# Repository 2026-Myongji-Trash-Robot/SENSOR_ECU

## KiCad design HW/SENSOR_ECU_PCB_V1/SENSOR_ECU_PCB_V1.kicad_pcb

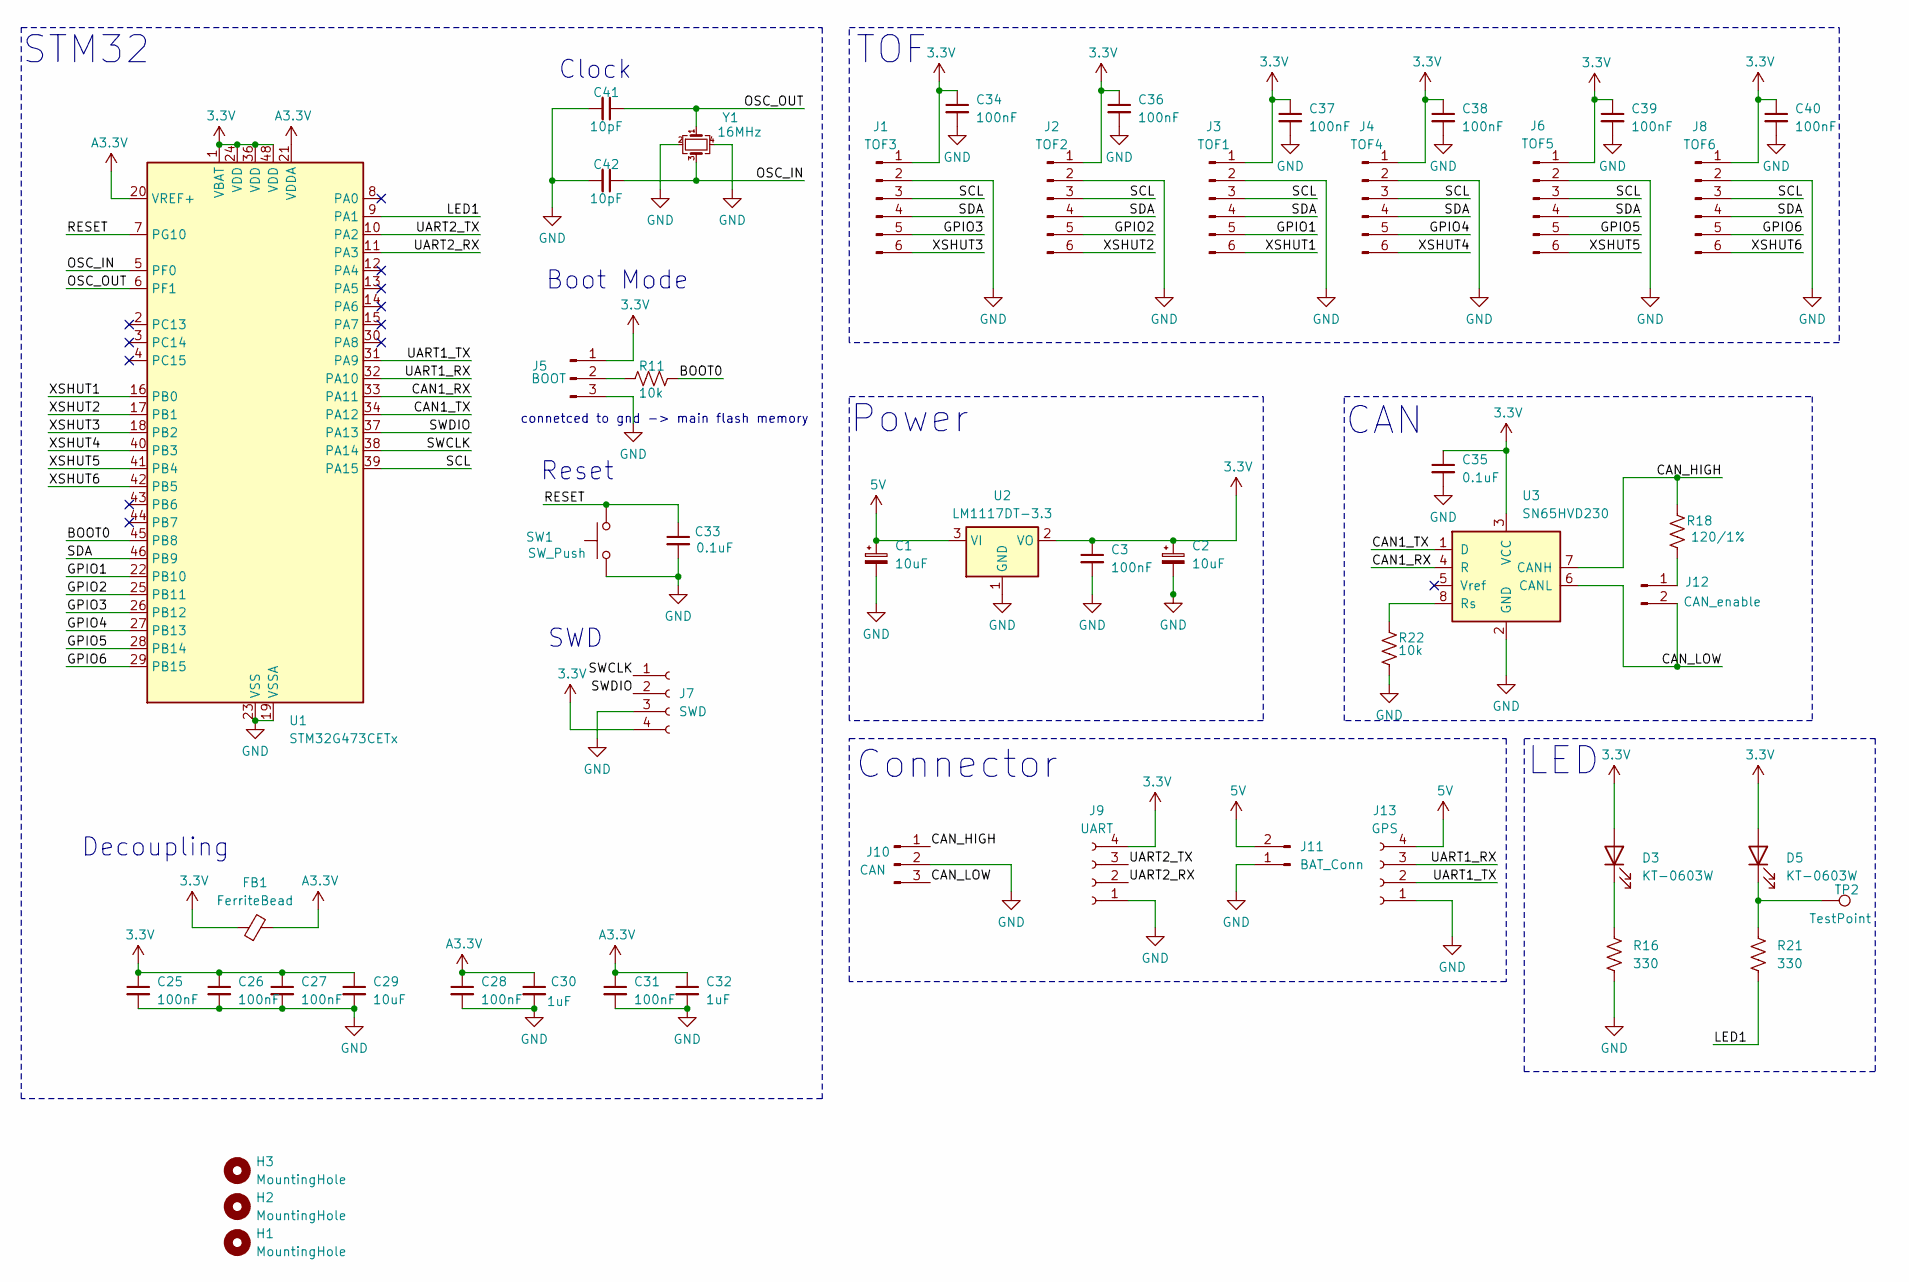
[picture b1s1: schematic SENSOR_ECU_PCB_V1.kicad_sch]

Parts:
C1, C2: 10uF; C_0603_1608Metric_Pad1.08x0.95mm_HandSolder
C3: 100nF; C_0603_1608Metric_Pad1.08x0.95mm_HandSolder
C25, C26, C27, C28, C34, C36, C37, C38: 100nF; C_0603_1608Metric; LCSC C14663
C29: 10uF; C_0603_1608Metric
C30, C32: 1uF; C_0603_1608Metric
C31, C39, C40: 100nF; C_0603_1608Metric
C33, C35: 0.1uF; C_0603_1608Metric
C41, C42: 10pF; C_0402_1005Metric_Pad0.74x0.62mm_HandSolder; LCSC C32949
D3, D5: KT-0603W; LED_0603_1608Metric; LCSC C2290
FB1: FerriteBead; L_0603_1608Metric; LCSC C1002
H1, H2, H3: MountingHole; MountingHole_3.2mm_M3
J1: TOF3; Molex_SPOX_5268-06A_1x06_P2.50mm_Horizontal
J2: TOF2; Molex_SPOX_5268-06A_1x06_P2.50mm_Horizontal
J3: TOF1; Molex_SPOX_5268-06A_1x06_P2.50mm_Horizontal
J4: TOF4; Molex_SPOX_5268-06A_1x06_P2.50mm_Horizontal
J5: BOOT; PinHeader_1x03_P2.54mm_Vertical
J6: TOF5; Molex_SPOX_5268-06A_1x06_P2.50mm_Horizontal
J7: SWD; PinHeader_1x04_P2.54mm_Horizontal
J8: TOF6; Molex_SPOX_5268-06A_1x06_P2.50mm_Horizontal
J9: UART; PinHeader_1x04_P2.54mm_Horizontal
J10: CAN; Wago_734-163_1x03_P3.50mm_Horizontal
J11: BAT_Conn; Wago_734-162_1x02_P3.50mm_Horizontal
J12: CAN_enable; PinHeader_1x02_P2.54mm_Vertical
J13: GPS; PinHeader_1x04_P2.54mm_Horizontal
R11, R22: 10k; R_0603_1608Metric; LCSC C15401
R16, R21: 330; R_0603_1608Metric; LCSC C23138
R18: 120/1%; R_0603_1608Metric; LCSC C22787
SW1: SW_Push; SW_PUSH_6mm_H7.3mm; LCSC C255812
TP2: TestPoint; TestPoint_Pad_D1.0mm
U1: STM32G473CETx; LQFP-48_7x7mm_P0.5mm; LCSC C730113
U2: LM1117DT-3.3; TO-252-2; LCSC C969102
U3: SN65HVD230; SOIC-8_3.9x4.9mm_P1.27mm; LCSC C12084
Y1: 16MHz; Crystal_SMD_3225-4Pin_3.2x2.5mm; LCSC C13738

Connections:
3.3V: C2.1, C3.1, C25.1, C26.1, C27.1, C29.1, C34.1, C35.1, C36.1, C37.1, C38.1, C39.1, C40.1, D3.2 (A), D5.2 (A), FB1.1, J1.1, J2.1, J3.1, J4.1, J5.1, J6.1, J7.4, J8.1, J9.4, U1.1 (VBAT), U1.24 (VDD), U1.36 (VDD), U1.48 (VDD), U2.2 (VO), U3.3 (VCC)
5V: C1.1, J11.2, J13.4, U2.3 (VI)
/BOOT0: R11.2, U1.45 (PB8)
/CAN1_RX: U1.33 (PA11), U3.4 (R)
/CAN1_TX: U1.34 (PA12), U3.1 (D)
/CAN_HIGH: J10.1, R18.2, U3.7 (CANH)
/CAN_LOW: J10.3, J12.2, U3.6 (CANL)
/GPIO1: J3.5, U1.22 (PB10)
/GPIO2: J2.5, U1.25 (PB11)
/GPIO3: J1.5, U1.26 (PB12)
/GPIO4: J4.5, U1.27 (PB13)
/GPIO5: J6.5, U1.28 (PB14)
/GPIO6: J8.5, U1.29 (PB15)
/LED1: R21.2, U1.9 (PA1)
/OSC_IN: C42.1, U1.5 (PF0), Y1.3
/OSC_OUT: C41.1, U1.6 (PF1), Y1.1
/RESET: C33.1, SW1.2, U1.7 (PG10)
/SCL: J1.3, J2.3, J3.3, J4.3, J6.3, J8.3, U1.39 (PA15)
/SDA: J1.4, J2.4, J3.4, J4.4, J6.4, J8.4, U1.46 (PB9)
/SWCLK: J7.1, U1.38 (PA14)
/SWDIO: J7.2, U1.37 (PA13)
/UART1_RX: J13.3, U1.32 (PA10)
/UART1_TX: J13.2, U1.31 (PA9)
/UART2_RX: J9.2, U1.11 (PA3)
/UART2_TX: J9.3, U1.10 (PA2)
/XSHUT1: J3.6, U1.16 (PB0)
/XSHUT2: J2.6, U1.17 (PB1)
/XSHUT3: J1.6, U1.18 (PB2)
/XSHUT4: J4.6, U1.40 (PB3)
/XSHUT5: J6.6, U1.41 (PB4)
/XSHUT6: J8.6, U1.42 (PB5)
A3.3V: C28.1, C30.1, C31.1, C32.1, FB1.2, U1.20 (VREF+), U1.21 (VDDA)
GND: C1.2, C2.2, C3.2, C25.2, C26.2, C27.2, C28.2, C29.2, C30.2, C31.2, C32.2, C33.2, C34.2, C35.2, C36.2, C37.2, C38.2, C39.2, C40.2, C41.2, C42.2, J1.2, J2.2, J3.2, J4.2, J5.3, J6.2, J7.3, J8.2, J9.1, J10.2, J11.1, J13.1, R16.2, R22.1, SW1.1, U1.19 (VSSA), U1.23 (VSS), U1.35 (VSS), U1.47 (VSS), U2.1 (GND), U3.2 (GND), Y1.2, Y1.4
unnamed: D3.1 (K), R16.1
unnamed: D5.1 (K), R21.1, TP2.1
unnamed: J5.2, R11.1
unnamed: J12.1, R18.1
unnamed: R22.2, U3.8 (Rs)

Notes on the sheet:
Connector
Decoupling
Reset
CAN
Clock
connetced to gnd -> main flash memory
Boot Mode
STM32
SWD
TOF
LED
Power

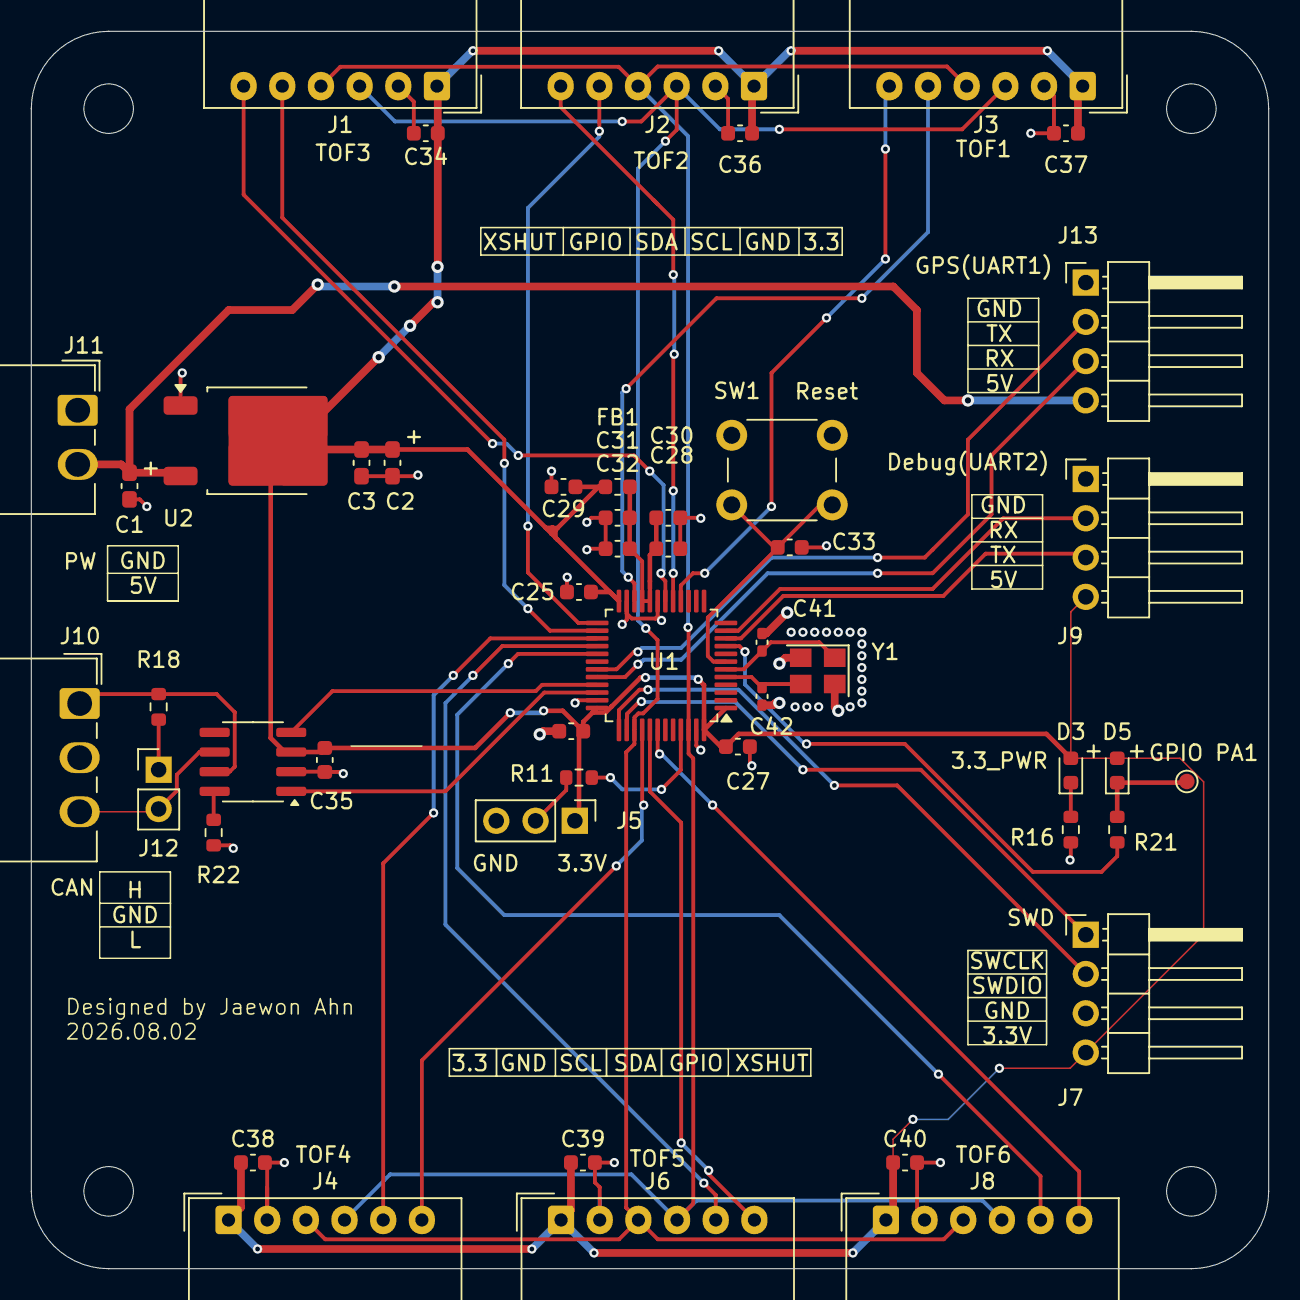
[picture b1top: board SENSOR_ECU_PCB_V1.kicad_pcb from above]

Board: 2 copper layers, 80.0 x 80.0 mm, 52 parts (0 on the bottom side), 38 nets.

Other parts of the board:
H4: MountingHole; MountingHole_3.2mm_M3

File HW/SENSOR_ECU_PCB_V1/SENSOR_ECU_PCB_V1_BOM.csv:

Reference,Qty,Value,Footprint,LCSC
"C1,C2",2,10uF,Capacitor_SMD:C_0603_1608Metric_Pad1.08x0.95mm_HandSolder,C7171
C3,1,100nF,Capacitor_SMD:C_0603_1608Metric_Pad1.08x0.95mm_HandSolder,C14663
"C25,C26,C27,C28,C34,C36,C37,C38",8,100nF,Capacitor_SMD:C_0603_1608Metric,C14663 
C29,1,10uF,Capacitor_SMD:C_0603_1608Metric,C19702
"C30,C32",2,1uF,Capacitor_SMD:C_0603_1608Metric,C15849
"C31,C39,C40",3,100nF,Capacitor_SMD:C_0603_1608Metric,C14663 
"C33,C35",2,0.1uF,Capacitor_SMD:C_0603_1608Metric,C14663 
"C41,C42",2,10pF,Capacitor_SMD:C_0402_1005Metric_Pad0.74x0.62mm_HandSolder,C32949
"D3,D5",2,KT-0603W,LED_SMD:LED_0603_1608Metric,C2290
FB1,1,FerriteBead,Inductor_SMD:L_0603_1608Metric,C1002
J1,1,TOF3,Connector_Molex:Molex_SPOX_5268-06A_1x06_P2.50mm_Horizontal,
J2,1,TOF2,Connector_Molex:Molex_SPOX_5268-06A_1x06_P2.50mm_Horizontal,
J3,1,TOF1,Connector_Molex:Molex_SPOX_5268-06A_1x06_P2.50mm_Horizontal,
J4,1,TOF4,Connector_Molex:Molex_SPOX_5268-06A_1x06_P2.50mm_Horizontal,
J5,1,BOOT,Connector_PinHeader_2.54mm:PinHeader_1x03_P2.54mm_Vertical,
J6,1,TOF5,Connector_Molex:Molex_SPOX_5268-06A_1x06_P2.50mm_Horizontal,
J7,1,SWD,Connector_PinHeader_2.54mm:PinHeader_1x04_P2.54mm_Horizontal,
J8,1,TOF6,Connector_Molex:Molex_SPOX_5268-06A_1x06_P2.50mm_Horizontal,
J9,1,UART,Connector_PinHeader_2.54mm:PinHeader_1x04_P2.54mm_Horizontal,
J10,1,CAN,Connector_Wago:Wago_734-163_1x03_P3.50mm_Horizontal,
J11,1,BAT_Conn,Connector_Wago:Wago_734-162_1x02_P3.50mm_Horizontal,
J12,1,CAN_enable,Connector_PinHeader_2.54mm:PinHeader_1x02_P2.54mm_Vertical,
J13,1,GPS,Connector_PinHeader_2.54mm:PinHeader_1x04_P2.54mm_Horizontal,
"R11,R22",2,10k,Resistor_SMD:R_0603_1608Metric,C15401
"R16,R21",2,330,Resistor_SMD:R_0603_1608Metric,C23138
R18,1,120/1%,Resistor_SMD:R_0603_1608Metric,C22787
SW1,1,SW_Push,Button_Switch_THT:SW_PUSH_6mm_H7.3mm,C255812
U1,1,STM32G473CETx,Package_QFP:LQFP-48_7x7mm_P0.5mm,C730113
U2,1,LM1117DT-3.3,Package_TO_SOT_SMD:TO-252-2,C969102
U3,1,SN65HVD230,Package_SO:SOIC-8_3.9x4.9mm_P1.27mm,C12084
Y1,1,16MHz,Crystal:Crystal_SMD_3225-4Pin_3.2x2.5mm,C13738
